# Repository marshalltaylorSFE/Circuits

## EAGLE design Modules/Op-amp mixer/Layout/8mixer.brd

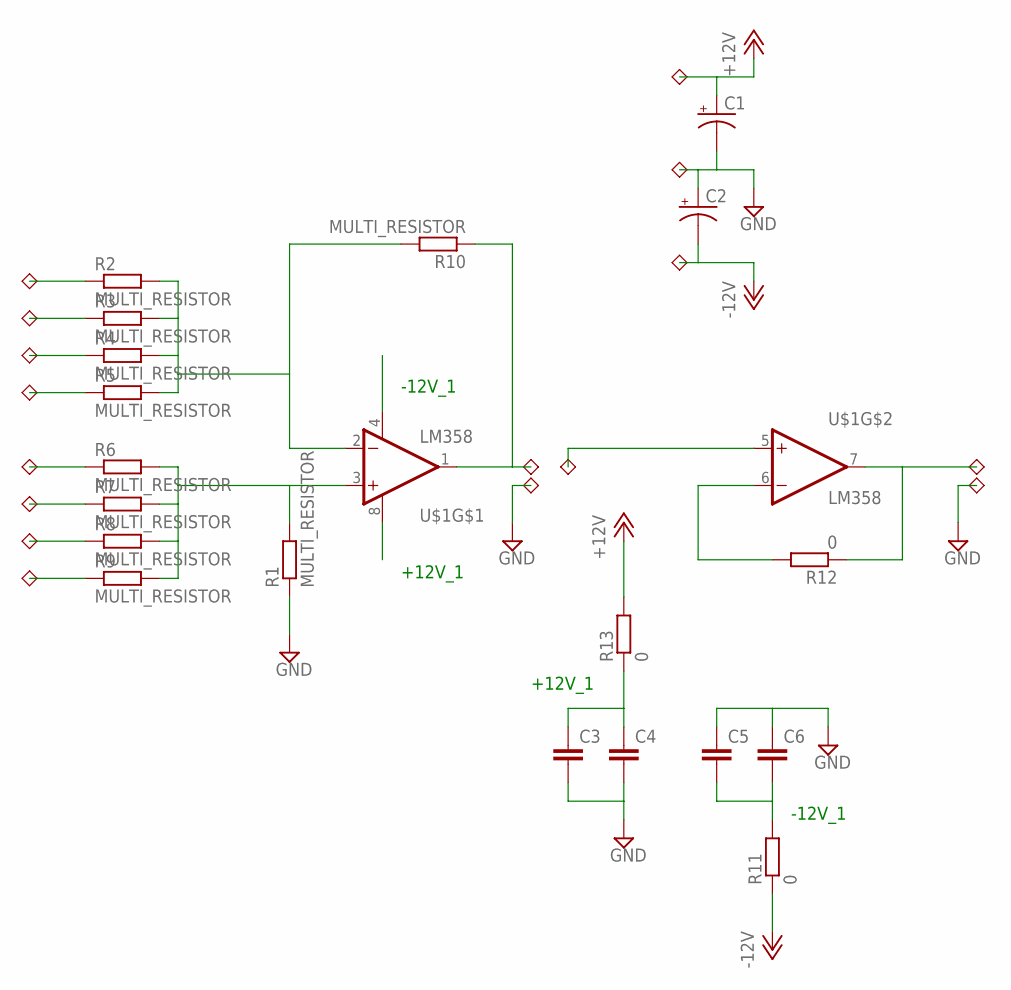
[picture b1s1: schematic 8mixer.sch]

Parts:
C1, C2: CPOL-USSMCE; SMC_E
C3, C4, C5, C6: C-EUC0805; C0805
R1, R2, R3, R4, R5, R6, R7, R8, R9, R10: MULTI_RESISTOR; MULTI_PAD
R11, R12, R13: 0; M1206
U$1: LM358; SO08
U$2, U$3, U$4, U$5, U$6, U$7, U$8, U$9, U$10, U$11, U$12, U$13, U$14, U$15, U$16, U$17: 1PIN; THUMBNAIL

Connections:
+12V: C1.+, R13.2, U$10.P$1
+12V_1: C3.1, C4.1, R13.1, U$1.8 (V+)
-12V: C2.-, R11.1, U$12.P$1
-12V_1: C5.2, C6.2, R11.2, U$1.4 (V-)
GND: C1.-, C2.+, C3.2, C4.2, C5.1, C6.1, R1.1, U$11.P$1, U$14.P$1, U$16.P$1
unnamed: R2.1, U$2.P$1
unnamed: R2.2, R3.2, R4.2, R5.2, R10.2, U$1.2 (-IN)
unnamed: R12.1, U$1.7 (OUT), U$15.P$1
unnamed: R3.1, U$3.P$1
unnamed: R4.1, U$4.P$1
unnamed: R5.1, U$5.P$1
unnamed: R6.1, U$6.P$1
unnamed: R7.1, U$7.P$1
unnamed: R8.1, U$8.P$1
unnamed: R9.1, U$9.P$1
unnamed: R12.2, U$1.6 (-IN)
unnamed: R1.2, R6.2, R7.2, R8.2, R9.2, U$1.3 (+IN)
unnamed: R10.1, U$1.1 (OUT), U$13.P$1
unnamed: U$1.5 (+IN), U$17.P$1

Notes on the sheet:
-12V_1
+12V_1

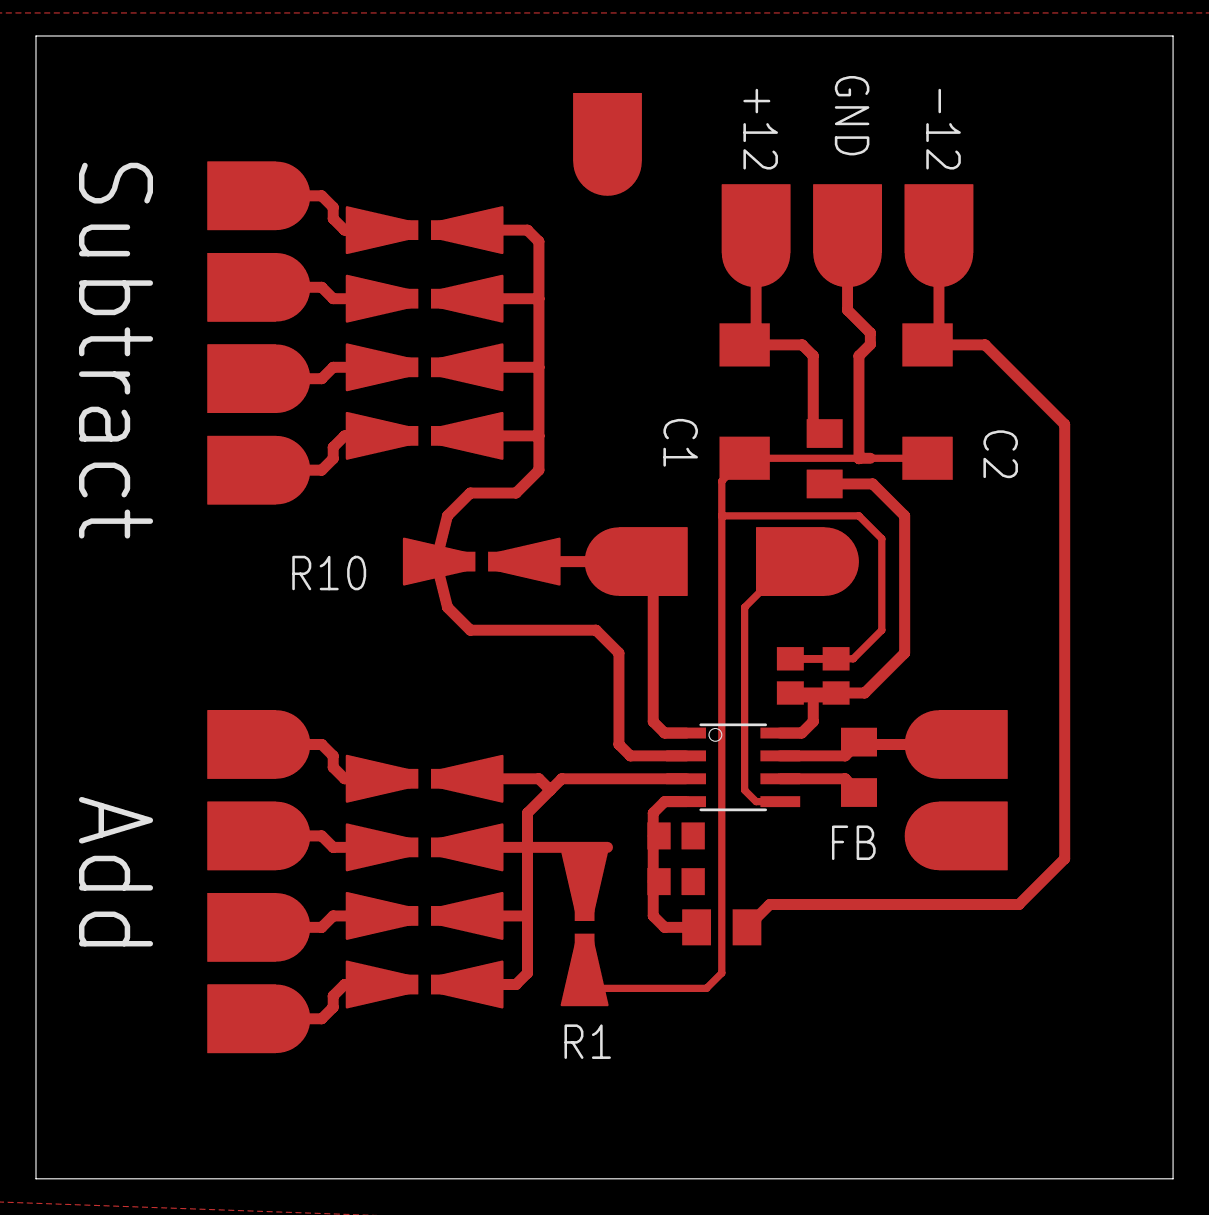
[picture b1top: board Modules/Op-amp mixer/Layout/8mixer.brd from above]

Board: 2 copper layers, 63.2 x 63.5 mm, 36 parts (0 on the bottom side), 19 nets.

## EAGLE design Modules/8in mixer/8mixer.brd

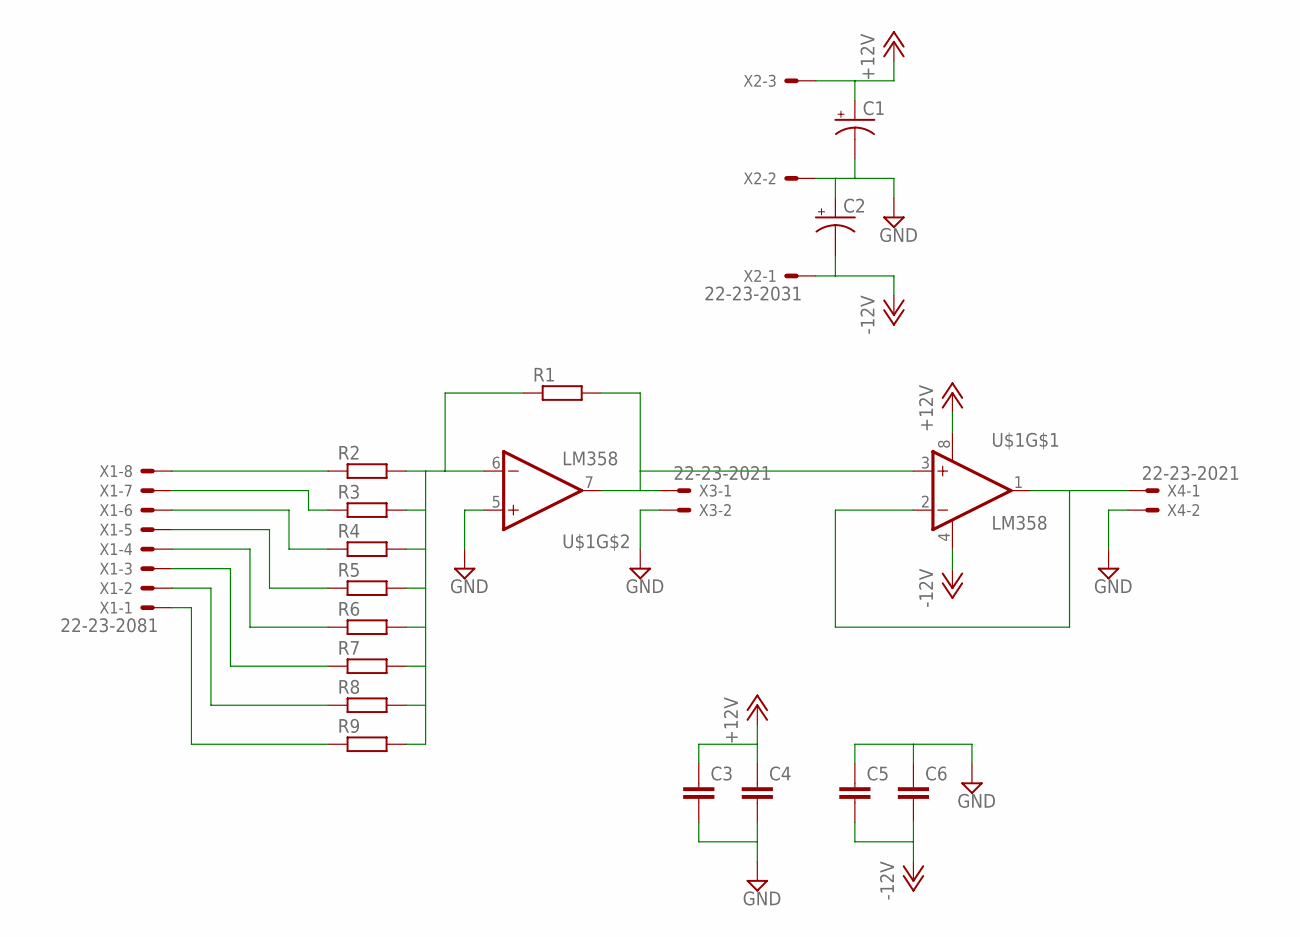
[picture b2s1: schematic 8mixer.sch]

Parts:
C1, C2: CPOL-USSMCE; SMC_E
C3, C4, C5, C6: C-EUC0603K; C0603K
R1, R2, R3, R4, R5, R6, R7, R8, R9: R-EU_R0603; R0603
U$1: LM358; SO08
X1: 22-23-2081
X2: 22-23-2031
X3, X4: 22-23-2021

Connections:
+12V: C1.+, C3.1, C4.1, U$1.8 (V+), X2.3
-12V: C2.-, C5.2, C6.2, U$1.4 (V-), X2.1
GND: C1.-, C2.+, C3.2, C4.2, C5.1, C6.1, U$1.5 (+IN), X2.2, X3.2, X4.2
unnamed: R1.1, R2.2, R3.2, R4.2, R5.2, R6.2, R7.2, R8.2, R9.2, U$1.6 (-IN)
unnamed: U$1.1 (OUT), U$1.2 (-IN), X4.1
unnamed: R2.1, X1.8
unnamed: R3.1, X1.7
unnamed: R4.1, X1.6
unnamed: R5.1, X1.5
unnamed: R6.1, X1.4
unnamed: R7.1, X1.3
unnamed: R8.1, X1.2
unnamed: R9.1, X1.1
unnamed: R1.2, U$1.3 (+IN), U$1.7 (OUT), X3.1

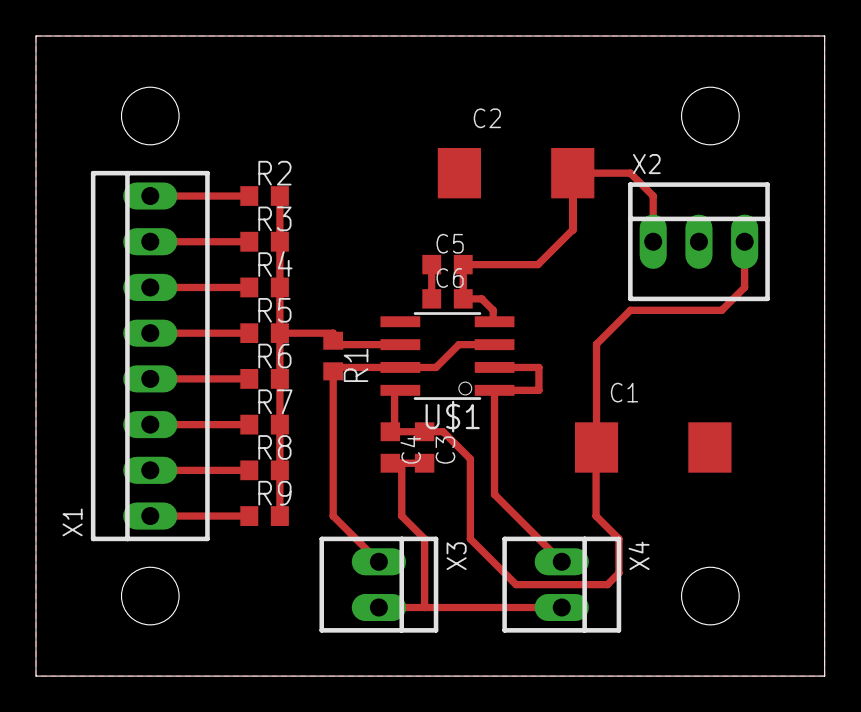
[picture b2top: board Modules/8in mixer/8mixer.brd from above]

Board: 2 copper layers, 43.8 x 35.6 mm, 20 parts (0 on the bottom side), 14 nets.

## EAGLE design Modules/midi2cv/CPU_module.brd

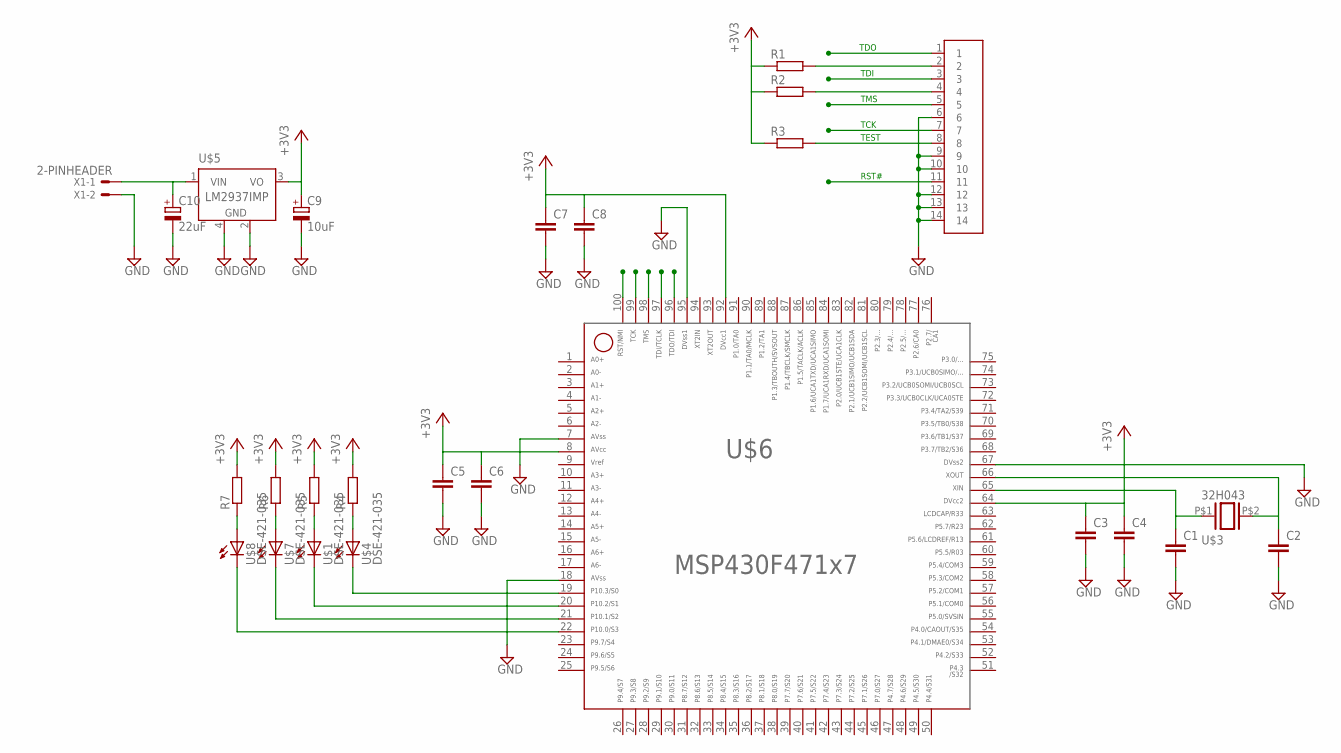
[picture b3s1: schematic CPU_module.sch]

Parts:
C1, C2, C3, C4, C5, C6, C7, C8: C-EUC0402; C0402
C9: 10uF; SMC_C
C10: 22uF; SMC_D
R1, R2, R3, R4, R5, R6, R7: R-EU_R0402; R0402
U$1, U$4, U$7, U$8: DSE-421-035; 2432
U$2: 2X7SMD_HEADER; 2X14SMDPADS
U$3: 32H043; XTAL-SMALL-4
U$5: LM2937IMP; SOT223
U$6: F471X7---PZ100; PZ100
X1: 2-PINHEADER; 22-23-2021

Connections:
+3V3: C3.1, C4.1, C5.1, C6.1, C7.1, C8.1, C9.+, R1.1, R2.1, R3.1, R4.2, R5.2, R6.2, R7.2, U$5.3 (VO), U$6.8, U$6.64, U$6.92
GND: C1.2, C2.2, C3.2, C4.2, C5.2, C6.2, C7.2, C8.2, C9.-, C10.-, U$2.6, U$2.9, U$2.10, U$2.12, U$2.13, U$2.14, U$5.2 (GND), U$5.4 (GND), U$6.7, U$6.18, U$6.67, U$6.95, X1.2
unnamed: R1.2, U$2.2
unnamed: C1.1, U$3.P$1 (1), U$6.65
unnamed: C2.1, U$3.P$2 (2), U$6.66
unnamed: R2.2, U$2.4
unnamed: U$6.22, U$8.MARKED (C)
unnamed: U$6.21, U$7.MARKED (C)
unnamed: U$1.MARKED (C), U$6.20
unnamed: U$4.MARKED (C), U$6.19
unnamed: R7.1, U$8.P$1 (A)
unnamed: R6.1, U$7.P$1 (A)
unnamed: R5.1, U$1.P$1 (A)
unnamed: R4.1, U$4.P$1 (A)
unnamed: C10.+, U$5.1 (VIN), X1.1
RST#: U$2.11, U$6.100
TCK: U$2.7, U$6.99
TDI: U$2.3, U$6.97
TDO: U$2.1, U$6.96
TEST: R3.2, U$2.8
TMS: U$2.5, U$6.98

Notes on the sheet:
TDO
TDI
TMS
TCK
TEST
RST#

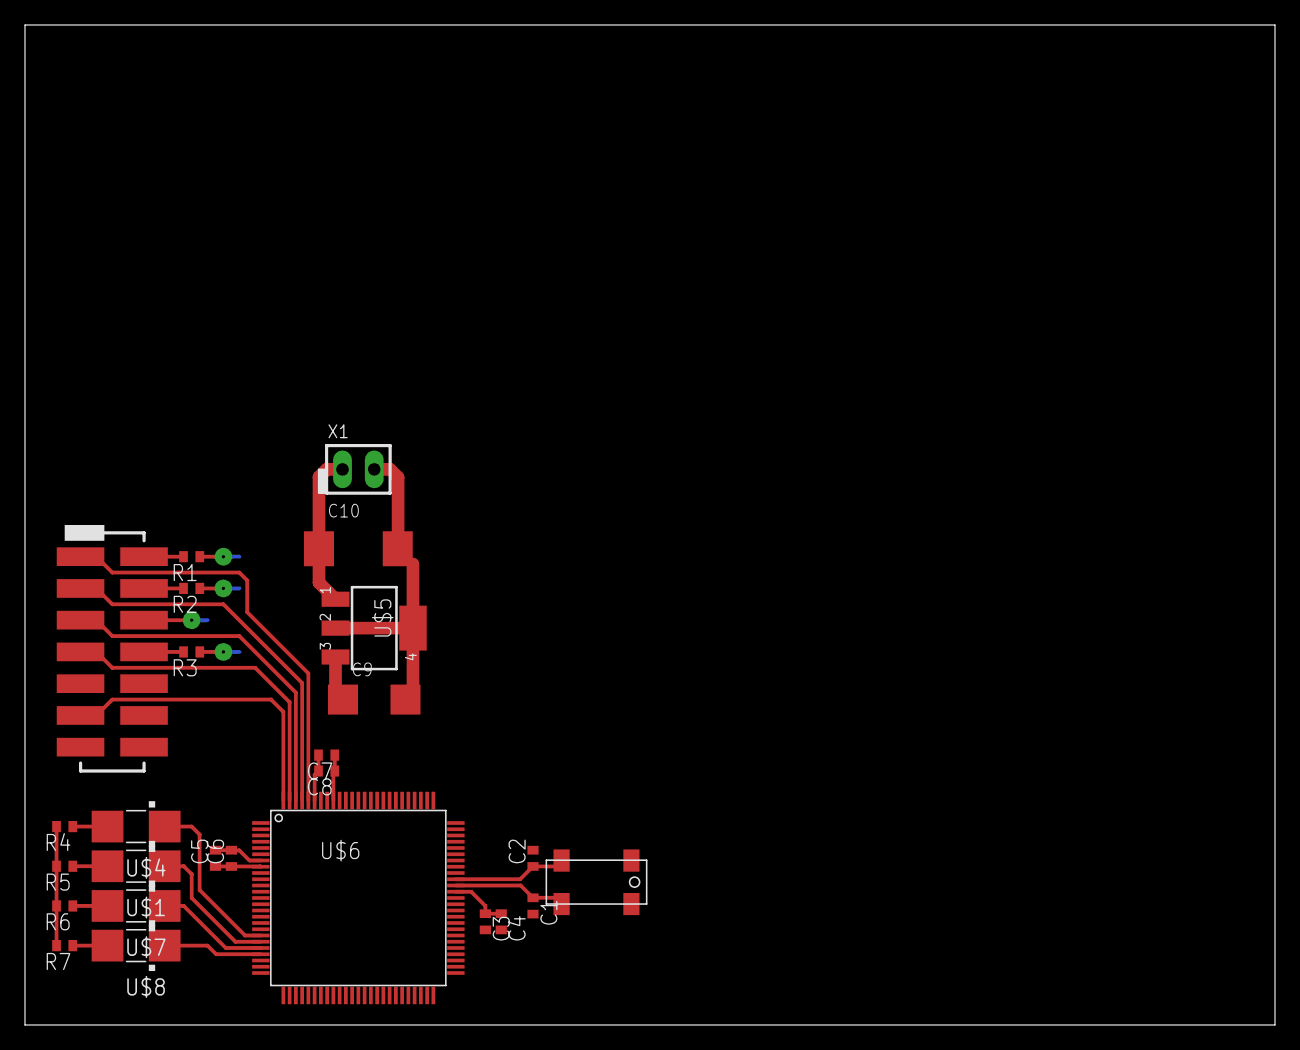
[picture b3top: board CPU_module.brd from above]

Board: 2 copper layers, 100.0 x 80.0 mm, 26 parts (0 on the bottom side), 21 nets.

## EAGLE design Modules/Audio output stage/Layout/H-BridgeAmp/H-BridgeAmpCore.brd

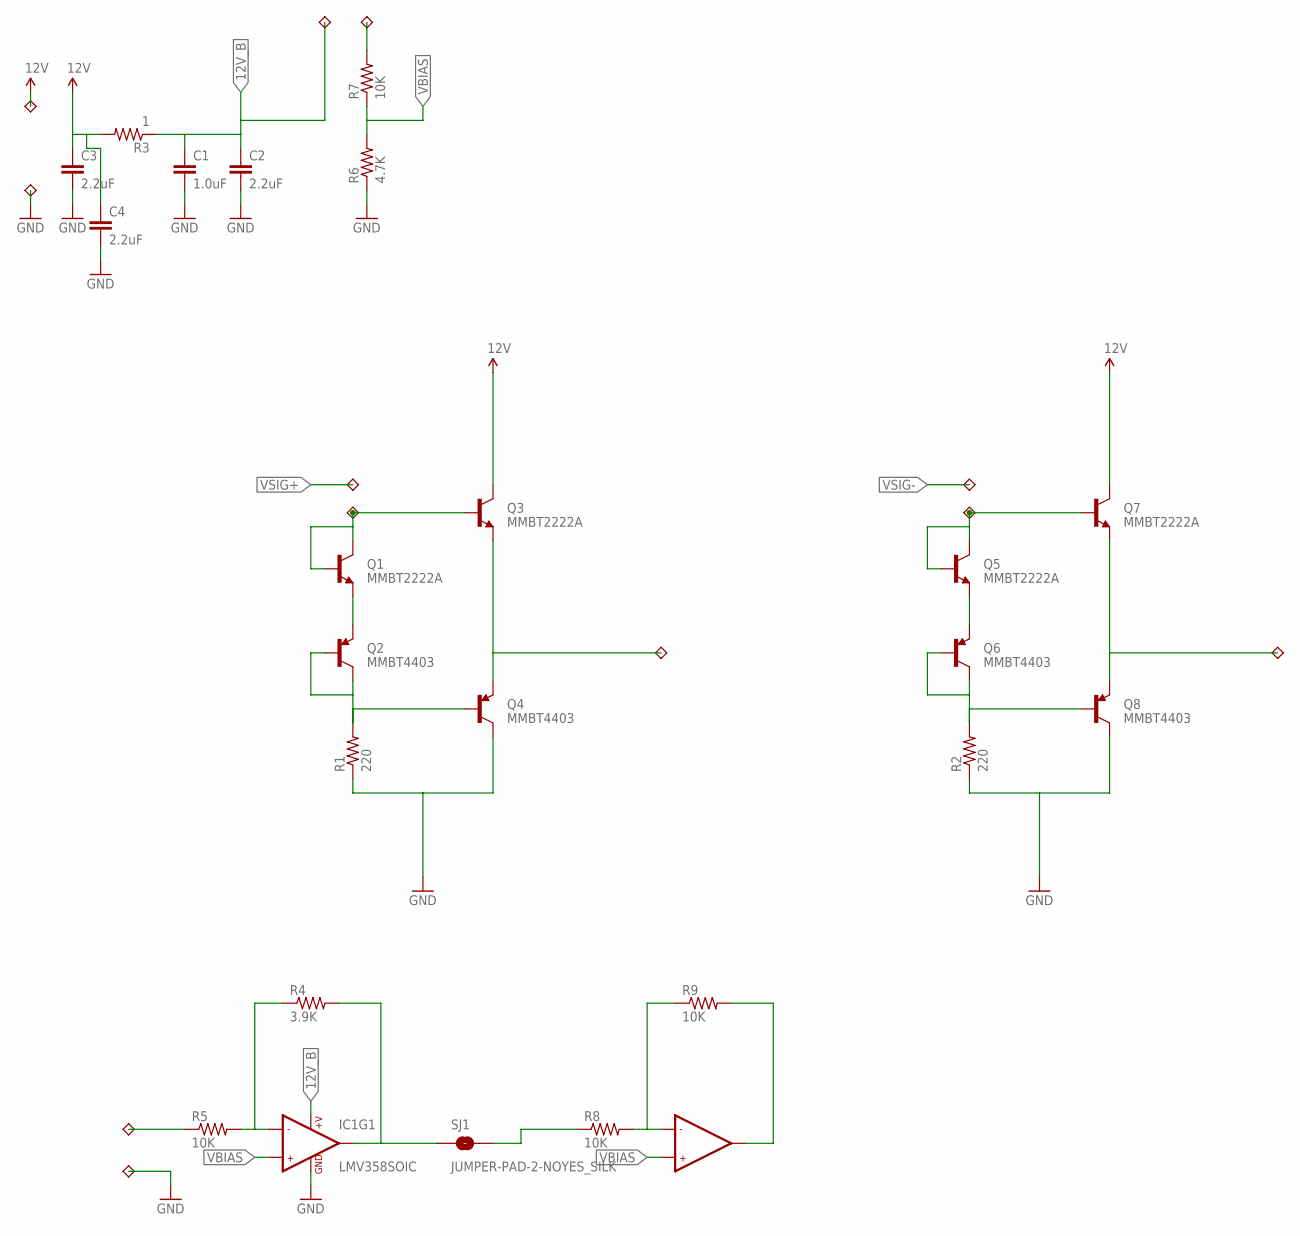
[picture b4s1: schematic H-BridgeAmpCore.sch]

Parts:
C1: 1.0uF; 0603-CAP
C2, C3, C4: 2.2uF; 0805-CAP
IC1: LMV358SOIC; SO08
Q1, Q3, Q5, Q7: MMBT2222A; SOT23-3
Q2, Q4, Q6, Q8: MMBT4403; SOT23-3
R1, R2: 220; 0603-RES
R3: 1; 0603-RES
R4: 3.9K; 0603
R5, R7, R8, R9: 10K; 0603-RES
R6: 4.7K; 0603-RES
SJ1: JUMPER-PAD-2-NOYES_SILK; PAD-JUMPER-2-NO_YES_SILK
U$1, U$2, U$3, U$4, U$5, U$6: 1PIN; THUMBNAIL
U$7, U$8, U$9, U$10, U$11, U$12: 1PINMINI; THUMBNAILMINI

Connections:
12V: C3.1, C4.1, Q3.3 (C), Q7.3 (C), R3.2, U$5.P$1
12V_B: C1.1, C2.1, IC1.8 (+V), R3.1, U$11.P$1
+IN: Q1.1 (B), Q1.3 (C), Q3.1 (B), U$9.P$1
-IN: Q5.1 (B), Q5.3 (C), Q7.1 (B), U$7.P$1
GND: C1.2, C2.2, C3.2, C4.2, IC1.4 (GND), Q4.3 (C), Q8.3 (C), R1.1, R2.1, R6.1, U$4.P$1, U$6.P$1
unnamed: R8.1, SJ1.2
unnamed: Q6.1 (B), Q6.3 (C), Q8.1 (B), R2.2
unnamed: R7.2, U$12.P$1
unnamed: Q2.1 (B), Q2.3 (C), Q4.1 (B), R1.2
unnamed: Q5.2 (E), Q6.2 (E)
unnamed: Q1.2 (E), Q2.2 (E)
unnamed: IC1.2 (-IN1), R4.1, R5.2
unnamed: IC1.6 (-IN2), R8.2, R9.1
unnamed: R5.1, U$3.P$1
OUT+: Q3.2 (E), Q4.2 (E), U$2.P$1
OUT-: Q7.2 (E), Q8.2 (E), U$1.P$1
VBIAS: IC1.3 (+IN1), IC1.5 (+IN2), R6.2, R7.1
VSIG+: IC1.1 (OUT1), R4.2, SJ1.1, U$10.P$1
VSIG-: IC1.7 (OUT2), R9.2, U$8.P$1

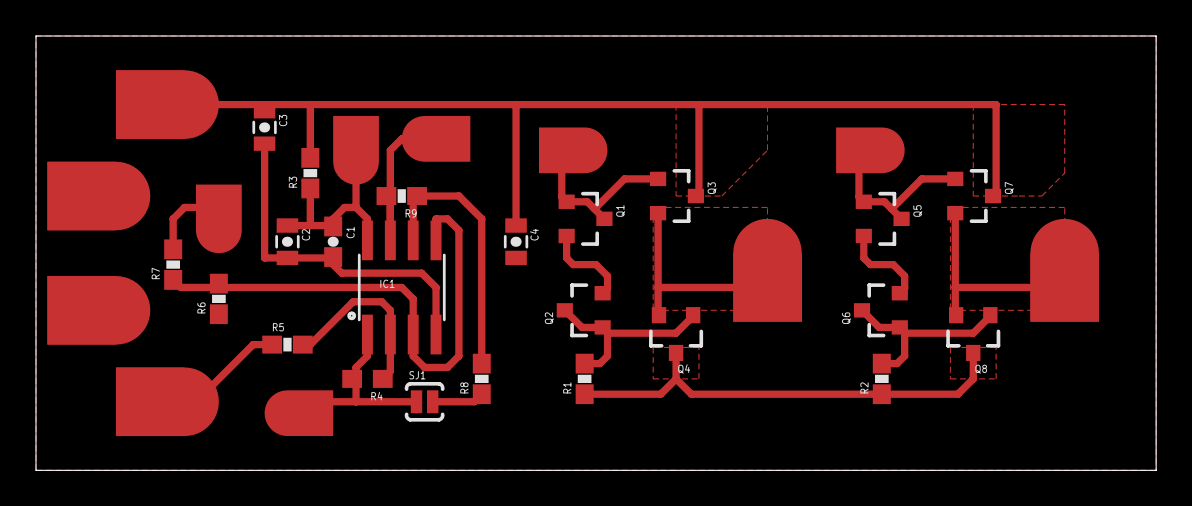
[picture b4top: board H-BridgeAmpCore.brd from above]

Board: 2 copper layers, 62.2 x 24.1 mm, 35 parts (0 on the bottom side), 19 nets.

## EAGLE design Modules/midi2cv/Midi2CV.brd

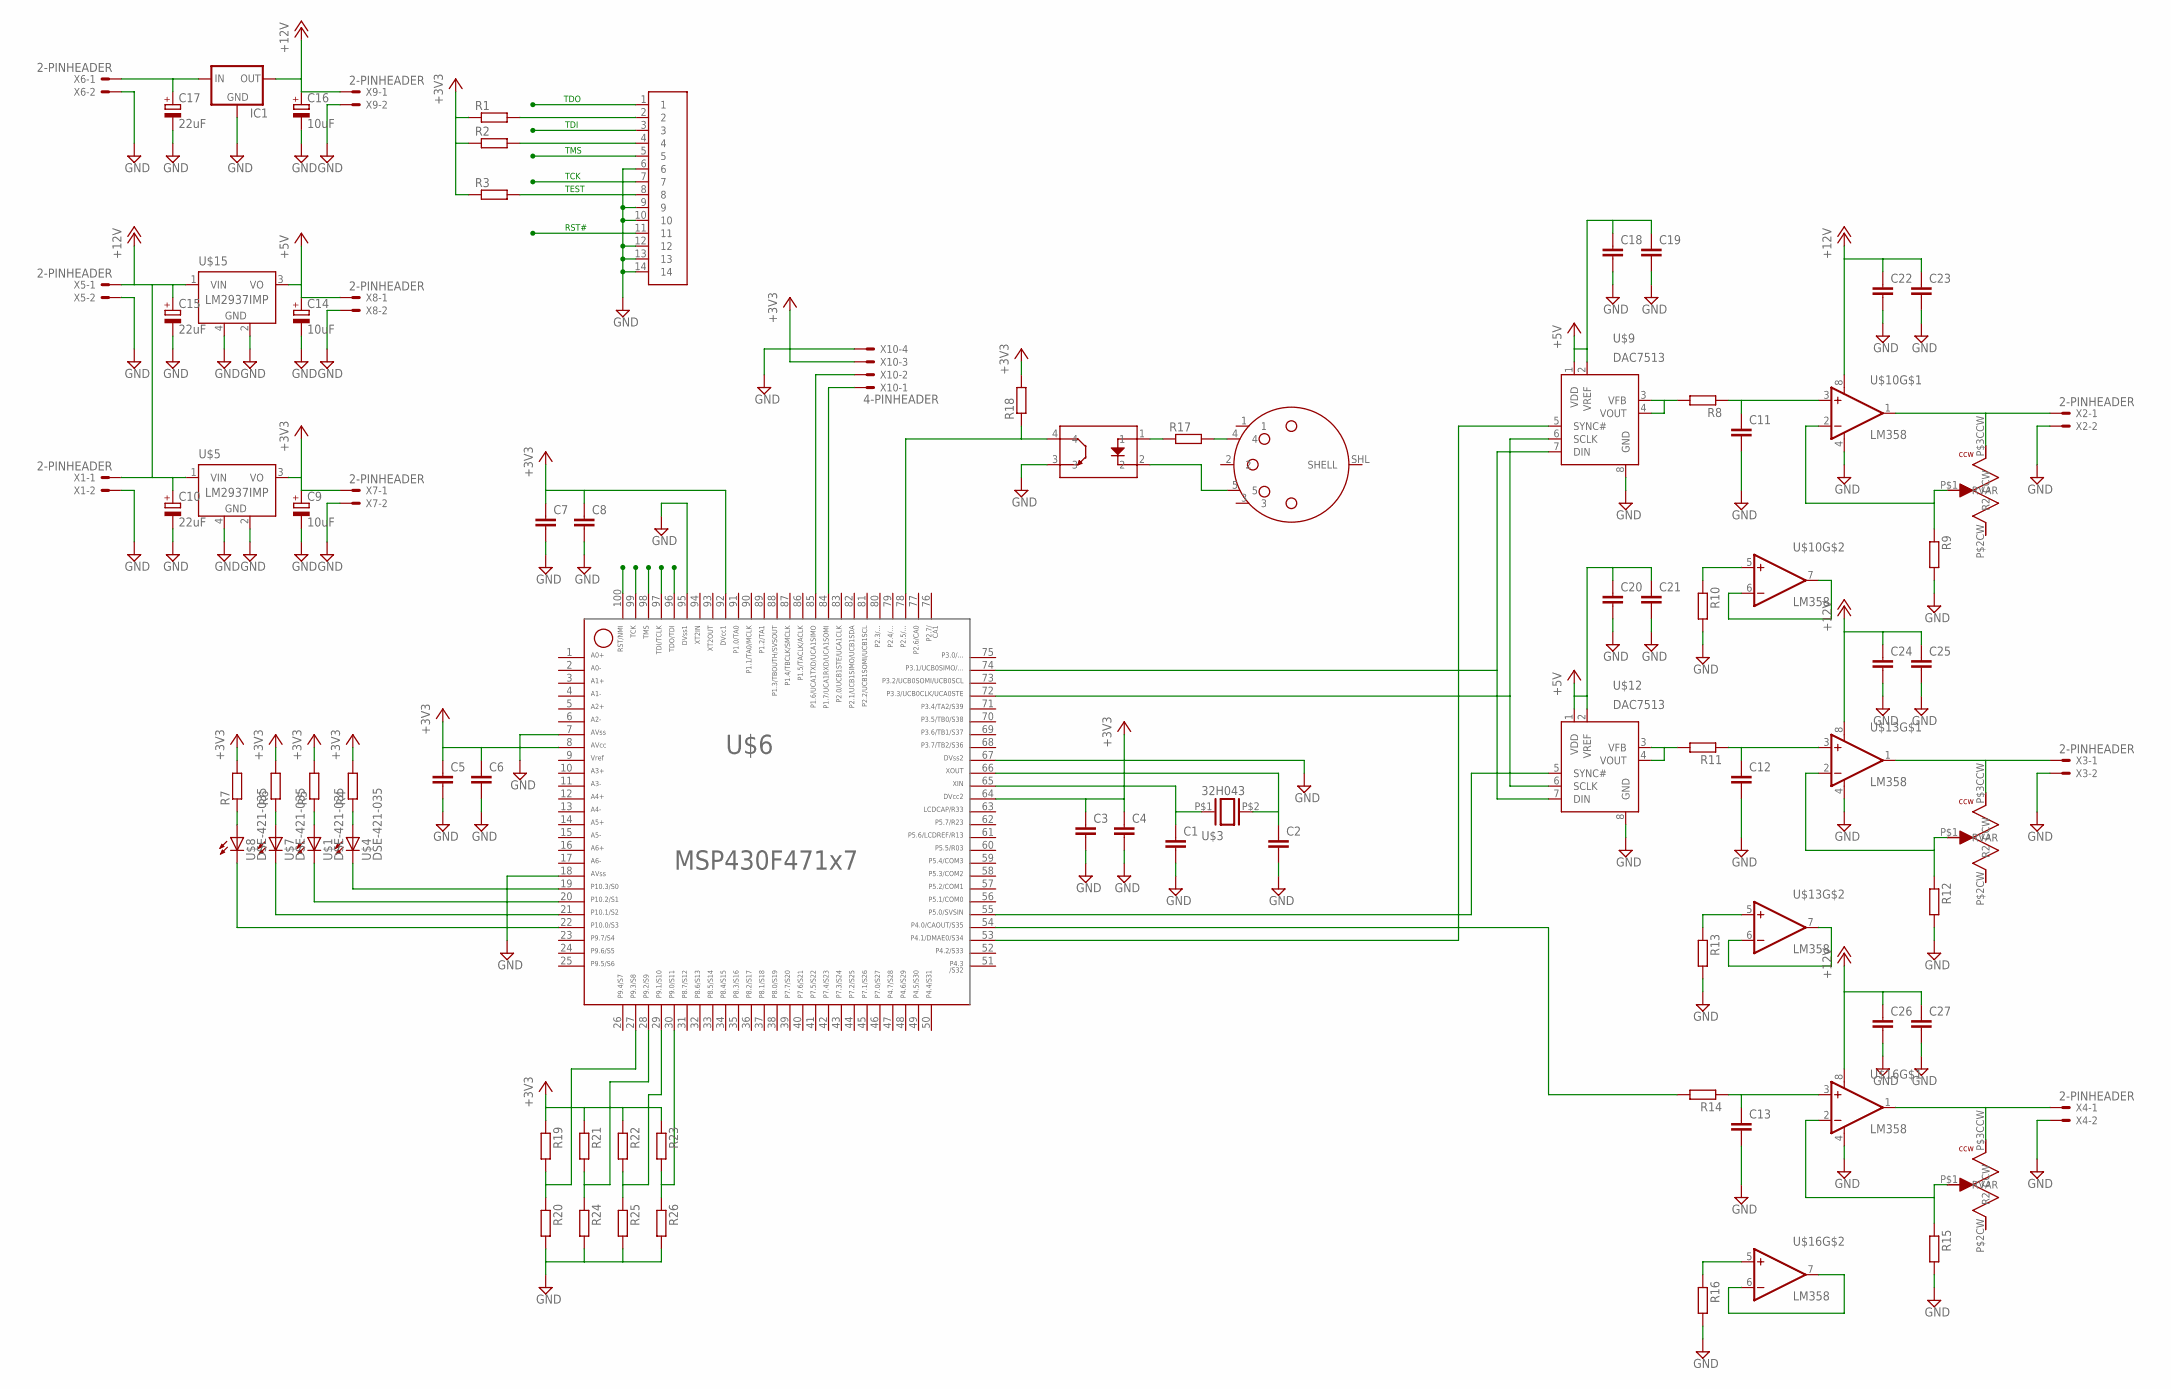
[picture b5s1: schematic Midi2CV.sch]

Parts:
C1, C2, C3, C4, C5, C6, C7, C8, C11, C12, C13, C18, C19, C20, C21, C22, C23, C24, C25, C26, C27: C-EUC0402; C0402
C9, C14, C16: 10uF; SMC_C
C10, C15, C17: 22uF; SMC_D
IC1: 78MXXS
R1, R2, R3, R4, R5, R6, R7, R8, R9, R10, R11, R12, R13, R14, R15, R16, R19, R20, R21, R22, R23, R24, R25, R26: R-EU_R0402; R0402
R17, R18: R-EU_R1206; R1206
U$1, U$4, U$7, U$8: DSE-421-035; 2432
U$2: 2X7SMD_HEADER; 2X14SMDPADS
U$3: 32H043; XTAL-SMALL-4
U$5, U$15: LM2937IMP; SOT223
U$6: F471X7---PZ100; PZ100
U$9, U$12: DAC7513; MSOP08
U$10, U$13, U$16: LM358; SO08
U$11, U$14, U$17: SMD-POT; POT_PADS
U$19: F2801A; LONG_TSOP
U$20: MIDI_VERT; DIN-5_VERT
X1, X2, X3, X4, X5, X6, X7, X8, X9: 2-PINHEADER; 22-23-2021
X10: 4-PINHEADER; 22-23-2041

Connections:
+3V3: C3.1, C4.1, C5.1, C6.1, C7.1, C8.1, C9.+, R1.1, R2.1, R3.1, R4.2, R5.2, R6.2, R7.2, R18.2, R19.1, R21.1, R22.1, R23.1, U$5.3 (VO), U$6.8, U$6.64, U$6.92, X7.1, X10.3
+5V: C14.+, C18.1, C19.1, C20.1, C21.1, U$9.1 (VDD), U$9.2 (VREF), U$12.1 (VDD), U$12.2 (VREF), U$15.3 (VO), X8.1
+12V: C10.+, C15.+, C16.+, C22.1, C23.1, C24.1, C25.1, C26.1, C27.1, IC1.OUT, U$5.1 (VIN), U$10.8 (V+), U$13.8 (V+), U$15.1 (VIN), U$16.8 (V+), X1.1, X5.1, X9.1
GND: C1.2, C2.2, C3.2, C4.2, C5.2, C6.2, C7.2, C8.2, C9.-, C10.-, C11.2, C12.2, C13.2, C14.-, C15.-, C16.-, C17.-, C18.2, C19.2, C20.2, C21.2, C22.2, C23.2, C24.2, C25.2, C26.2, C27.2, IC1.GND, R9.2, R10.2, R12.2, R13.2, R15.2, R16.2, R20.2, R24.2, R25.2, R26.2, U$2.6, U$2.9, U$2.10, U$2.12, U$2.13, U$2.14, U$5.2 (GND), U$5.4 (GND), U$6.7, U$6.18, U$6.67, U$6.95, U$9.8 (GND), U$10.4 (V-), U$12.8 (GND), U$13.4 (V-), U$15.2 (GND), U$15.4 (GND), U$16.4 (V-), U$19.3, X1.2, X2.2, X3.2, X4.2, X5.2, X6.2, X7.2, X8.2, X9.2, X10.4
unnamed: R1.2, U$2.2
unnamed: C1.1, U$3.P$1 (1), U$6.65
unnamed: C2.1, U$3.P$2 (2), U$6.66
unnamed: R2.2, U$2.4
unnamed: U$6.22, U$8.MARKED (C)
unnamed: U$6.21, U$7.MARKED (C)
unnamed: U$1.MARKED (C), U$6.20
unnamed: U$4.MARKED (C), U$6.19
unnamed: R7.1, U$8.P$1 (A)
unnamed: R6.1, U$7.P$1 (A)
unnamed: R5.1, U$1.P$1 (A)
unnamed: R4.1, U$4.P$1 (A)
unnamed: U$6.84, X10.1
unnamed: R8.2, U$9.3 (VFB), U$9.4 (VOUT)
unnamed: U$10.6 (-IN), U$10.7 (OUT)
unnamed: C11.1, R8.1, U$10.3 (+IN)
unnamed: R9.1, U$10.2 (-IN), U$11.P$1 (RVAR)
unnamed: U$10.1 (OUT), U$11.P$3CCW (CCW), X2.1
unnamed: R11.2, U$12.3 (VFB), U$12.4 (VOUT)
unnamed: R10.1, U$10.5 (+IN)
unnamed: U$13.6 (-IN), U$13.7 (OUT)
unnamed: C12.1, R11.1, U$13.3 (+IN)
unnamed: R12.1, U$13.2 (-IN), U$14.P$1 (RVAR)
unnamed: U$13.1 (OUT), U$14.P$3CCW (CCW), X3.1
unnamed: R13.1, U$13.5 (+IN)
unnamed: R14.2, U$6.54
unnamed: U$16.6 (-IN), U$16.7 (OUT)
unnamed: C13.1, R14.1, U$16.3 (+IN)
unnamed: R15.1, U$16.2 (-IN), U$17.P$1 (RVAR)
unnamed: U$16.1 (OUT), U$17.P$3CCW (CCW), X4.1
unnamed: R16.1, U$16.5 (+IN)
unnamed: U$6.85, X10.2
unnamed: U$6.72, U$9.6 (SCLK), U$12.6 (SCLK)
unnamed: U$6.74, U$9.7 (DIN), U$12.7 (DIN)
unnamed: R17.2, U$20.4
unnamed: U$6.53, U$9.5 (SYNC#)
unnamed: U$6.55, U$12.5 (SYNC#)
unnamed: R17.1, U$19.1
unnamed: U$19.2, U$20.5
unnamed: R18.1, U$6.78, U$19.4
unnamed: C17.+, IC1.IN, X6.1
unnamed: R19.2, R20.1, U$6.27
unnamed: R21.2, R24.1, U$6.28
unnamed: R22.2, R25.1, U$6.29
unnamed: R23.2, R26.1, U$6.30
RST#: U$2.11, U$6.100
TCK: U$2.7, U$6.99
TDI: U$2.3, U$6.97
TDO: U$2.1, U$6.96
TEST: R3.2, U$2.8
TMS: U$2.5, U$6.98

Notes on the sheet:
TDO
TDI
TMS
TCK
TEST
RST#

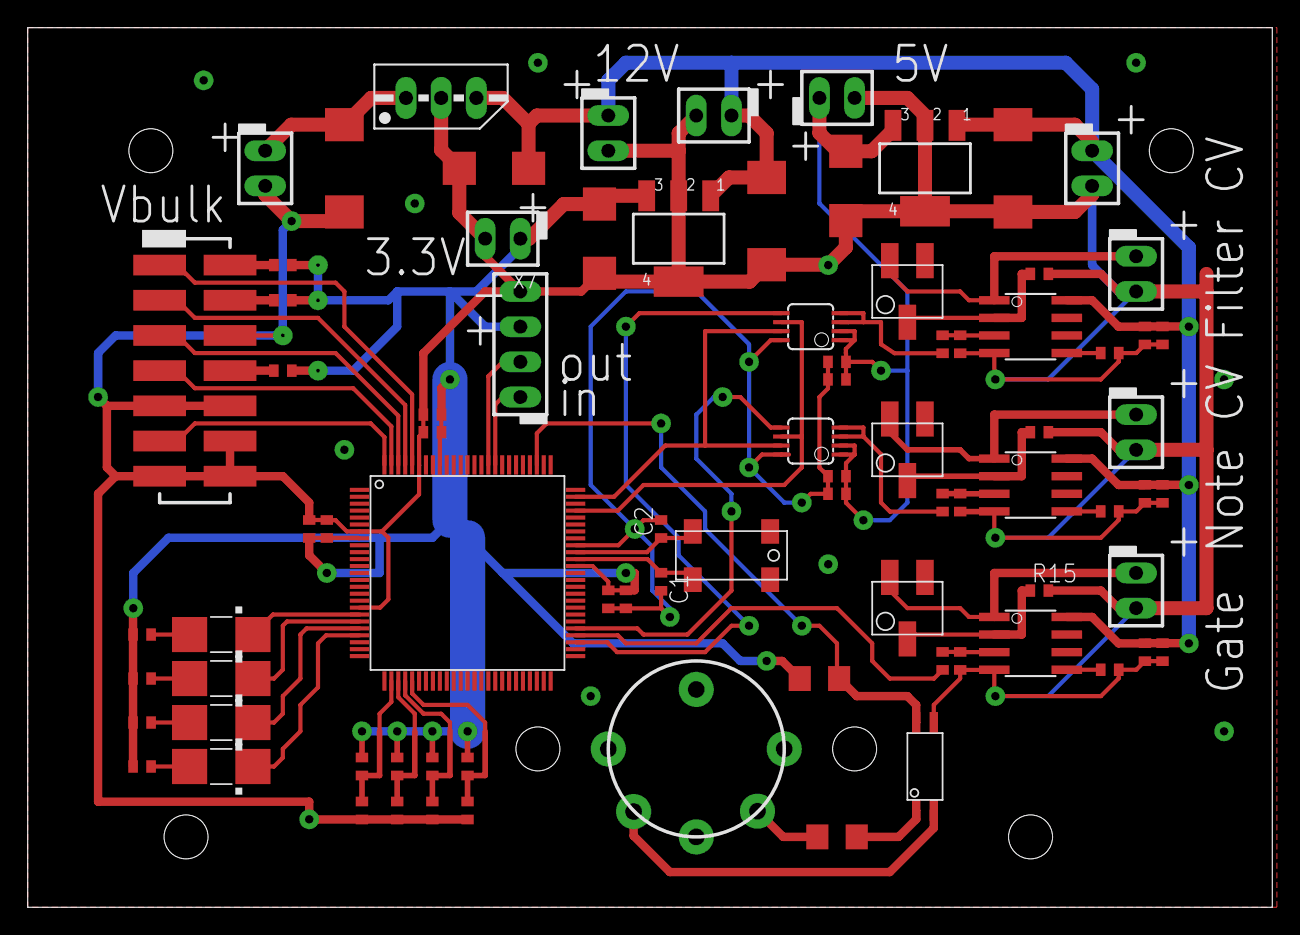
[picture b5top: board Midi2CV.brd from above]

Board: 2 copper layers, 89.8 x 63.5 mm, 83 parts (0 on the bottom side), 55 nets.

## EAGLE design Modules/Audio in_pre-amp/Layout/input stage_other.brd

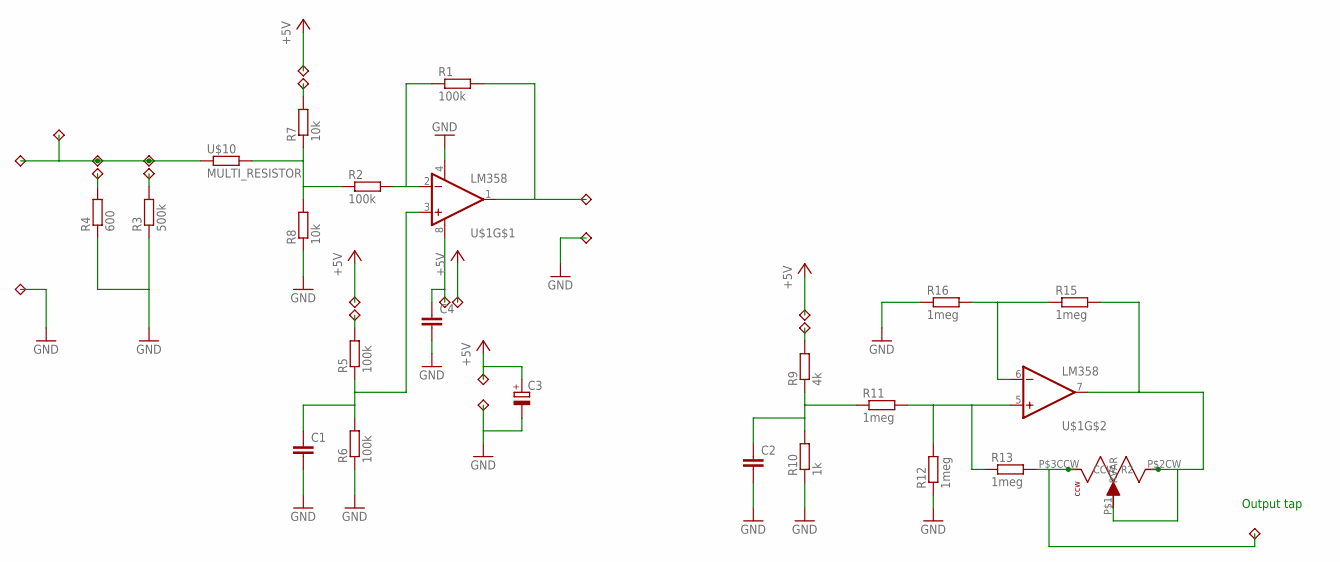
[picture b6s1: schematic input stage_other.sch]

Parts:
C1, C2, C4: C-EUC0603; C0603
C3: CPOL-EUC/6032-28R; C/6032-28R
R1, R2, R5, R6: 100k; R0603
R3: 500k; R0603
R4: 600; R0603
R7, R8: 10k; R0603
R9: 4k; R0603
R10: 1k; R0603
R11, R12, R13, R15, R16: 1meg; R0603
U$1: LM358; SO08
U$2, U$3, U$4, U$5, U$6, U$7, U$8, U$9, U$11, U$12, U$13, U$14: 1PIN; THUMBNAIL
U$10: MULTI_RESISTOR; MULTI_PAD
U$15: SMD-POT; POT_PADS
U$16, U$17, U$18, U$19, U$20, U$21, U$22, U$23: 1PIN_SM; THUMBNAIL_SM

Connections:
+5V: C3.+, U$2.P$1, U$17.P$1, U$19.P$1, U$21.P$1, U$23.P$1
GND: C1.2, C2.2, C3.-, C4.2, R3.1, R4.1, R6.1, R8.1, R10.1, R12.1, R16.1, U$1.4 (V-), U$3.P$1, U$8.P$1, U$9.P$1
unnamed: C1.1, R5.1, R6.2, U$1.3 (+IN)
unnamed: R1.1, R2.2, U$1.2 (-IN)
unnamed: U$5.P$1, U$6.P$1, U$10.1, U$12.P$1, U$13.P$1
unnamed: R1.2, U$1.1 (OUT), U$4.P$1
unnamed: R4.2, U$7.P$1
unnamed: R2.1, R7.1, R8.2, U$10.2
unnamed: R3.2, U$11.P$1
unnamed: C2.1, R9.1, R10.2, R11.1
unnamed: R15.1, R16.2, U$1.6 (-IN)
unnamed: R15.2, U$1.7 (OUT), U$15.P$1 (RVAR), U$15.P$2CW (R2)
unnamed: R13.2, U$14.P$1, U$15.P$3CCW (CCW)
unnamed: R11.2, R12.2, R13.1, U$1.5 (+IN)
unnamed: R9.2, U$16.P$1
unnamed: R7.2, U$18.P$1
unnamed: R5.2, U$20.P$1
unnamed: C4.1, U$1.8 (V+), U$22.P$1

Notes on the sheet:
Output tap

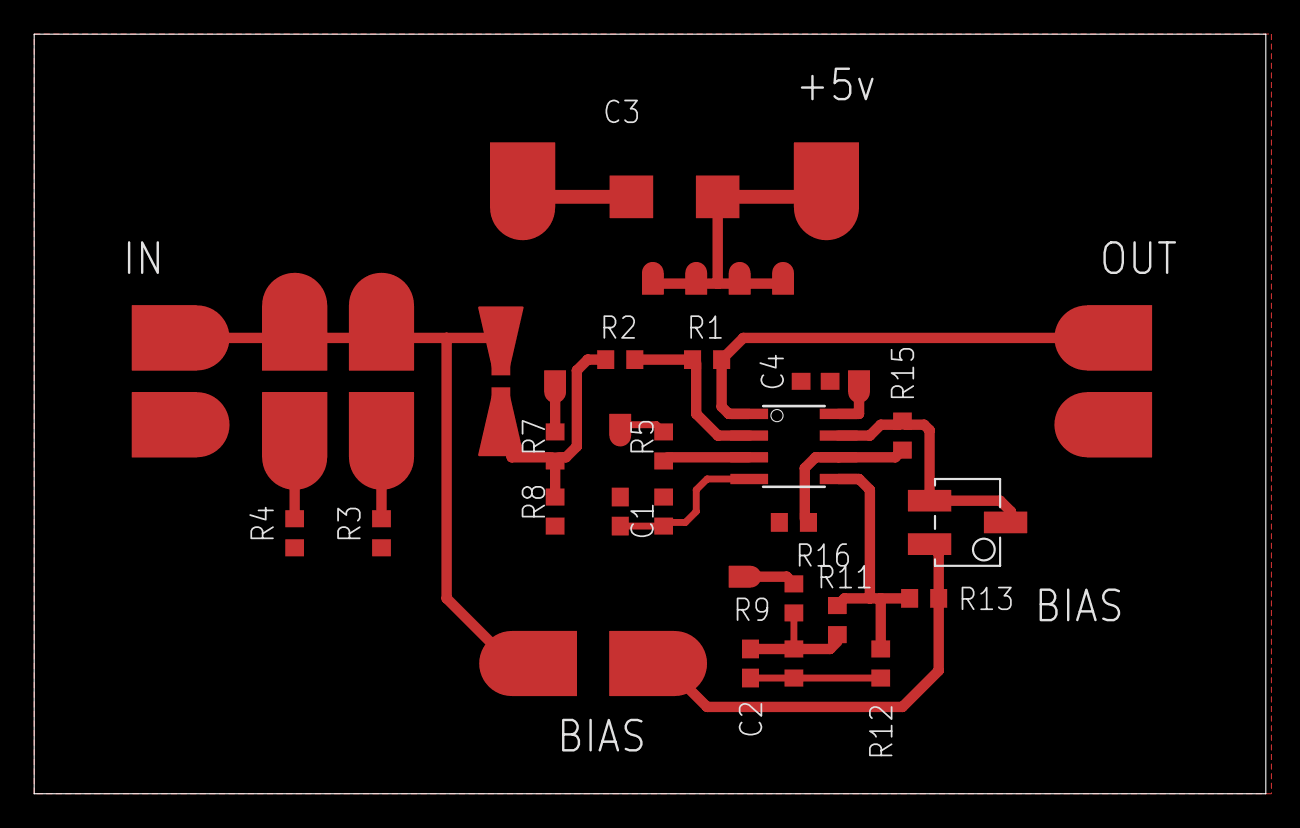
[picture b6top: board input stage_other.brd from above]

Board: 2 copper layers, 72.1 x 44.4 mm, 42 parts (0 on the bottom side), 18 nets.

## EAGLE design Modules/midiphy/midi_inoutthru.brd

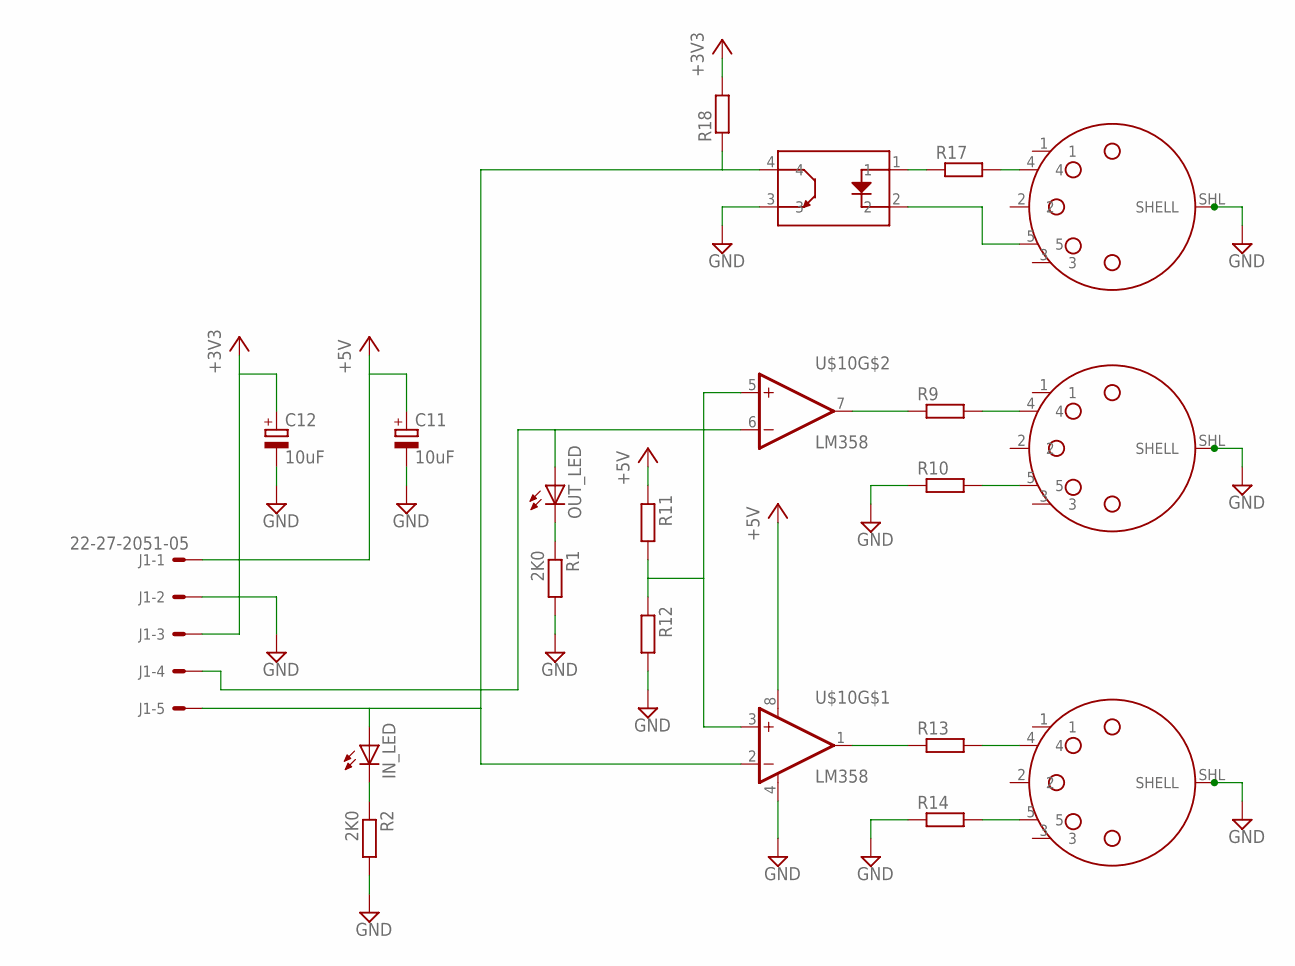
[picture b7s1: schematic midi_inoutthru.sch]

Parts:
C11, C12: 10uF; SMC_C
IN_LED: LEDCHIP-LED0805; CHIP-LED0805
J1: 22-27-2051-05; 6410-05
OUT_LED: LEDCHIP-LED0805; CHIP-LED0805
R1, R2: 2K0; R0402
R9, R10, R13, R14, R17, R18: R-EU_R1206; R1206
R11, R12: R-EU_R0402; R0402
U$9, U$11, U$20: MIDI_VERT; DIN-5_VERT
U$10: LM358; SO08
U$19: F2801A; LONG_TSOP

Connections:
+3V3: C12.+, J1.3, R18.2
+5V: C11.+, J1.1, R11.1, U$10.8 (V+)
GND: C11.-, C12.-, J1.2, R1.2, R2.2, R10.1, R12.2, R14.1, U$9.SHL (SHELL), U$10.4 (V-), U$11.SHL (SHELL), U$19.3, U$20.SHL (SHELL)
unnamed: IN_LED.C, R2.1
unnamed: OUT_LED.C, R1.1
unnamed: R10.2, U$9.5
unnamed: R9.2, U$9.4
unnamed: R9.1, U$10.7 (OUT)
unnamed: J1.4, OUT_LED.A, U$10.6 (-IN)
unnamed: R11.2, R12.1, U$10.3 (+IN), U$10.5 (+IN)
unnamed: R14.2, U$11.5
unnamed: R13.2, U$11.4
unnamed: R13.1, U$10.1 (OUT)
unnamed: R17.2, U$20.4
unnamed: R17.1, U$19.1
unnamed: U$19.2, U$20.5
unnamed: IN_LED.A, J1.5, R18.1, U$10.2 (-IN), U$19.4

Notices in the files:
parts and their libraries:
SparkFun-DiscreteSemi: Licensing: Creative Commons ShareAlike 4.0 International - https://creativecommons.org/licenses/by-sa/4.0
